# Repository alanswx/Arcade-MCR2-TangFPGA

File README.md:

# Bally Midway MCR2 Arcade Core for Gowin Tang FPGAs

Standalone port of the Bally Midway MCR arcade families for Sipeed Tang
FPGA boards — no MiSTer/HPS required. **MCR-2** (Tron, Domino Man,
Satan's Hollow, Wacko, Kozmik Kroozr, Two Tigers), **MCR-3/91490**
(Tapper — hardware-verified — plus Timber and Discs of Tron), and
**MCR-1** (Kick, Kickman, Solar Fox; builds, unverified). The flagship
target is the **Tang Console 60K**: each family's games in one bitstream,
selected at runtime from an on-screen menu, ROMs loaded from a single
microSD card shared by every family (pack format v2). The roadmap toward
the full-series multi-core jukebox is at the top of TODO.md.

| Board | Status |
|---|---|
| **Tang Console 60K** (GW5AT-60) | MCR-2: all six games + OSD menu. MCR-3: Tapper working (SDRAM sprites), Timber/DoT staged. 720p HDMI with audio (DDR3 framebuffer); analog RGB at 31/15 kHz for real cabinets; USB gamepad; SD ROM loading; <10 s watchdog-guarded cold boot |
| Tang Primer 25K (GW5A-25) | Domino Man over HDMI (single game per build, BSRAM-limited) |
| Tang Console 138K (GW5AST-138) | Stale — needs the 60K backport |

New here? Read [handoff_v7_jukebox.md](handoff_v7_jukebox.md) for the
current platform state and runway.

Deeper docs: build gotchas and architecture notes in [CLAUDE.md](CLAUDE.md),
open issues in [TODO.md](TODO.md), bench hookup in
[docs/bench_wiring.md](docs/bench_wiring.md), cabinet shield spec in
[docs/universal_mcr_shield_spec.md](docs/universal_mcr_shield_spec.md),
porting plan for the other MCR generations in
[docs/mcr_core_roadmap.md](docs/mcr_core_roadmap.md).

---

## 1. Generate the ROM hex tables

ROM zips (MAME sets) go in `roms/` — they are **not** in the repo. Then,
from the repo root:

```sh
python3 tools/merge_roms.py tron     # or domino / shollow / wacko / kroozr / twotiger
```

This writes the `rom_*.hex` tables the build bakes into BSRAM and sets the
board's `game_config.vh`. On the 60K the baked game only decides **what
boots with no SD card** — every game is reachable at runtime from the OSD.

## 2. Build

Headless (recommended; macOS paths shown — see CLAUDE.md for why the IDE
flow needs extra care):

```sh
GWLIB=/Applications/GowinIDE.app/Contents/Resources/Gowin_EDA/IDE/lib
GW=/Applications/GowinIDE.app/Contents/Resources/Gowin_EDA/IDE/bin/gw_sh
cd mcr2_console60k
DYLD_LIBRARY_PATH="$GWLIB" DYLD_FRAMEWORK_PATH="$GWLIB" "$GW" build.tcl
```

The bitstream lands at `mcr2_console60k/impl/pnr/mcr2_console60k.fs`.
Prebuilt images for all six games are kept in `bitstreams/`.

IDE builds work too (open `mcr2_console60k/mcr2_console60k.gprj`, Run All)
but several project settings must be exactly right — read the Gotchas
table in CLAUDE.md first; in particular **Place & Route → Place Option
must be 2** or HDMI silently dies.

## 3. Flash the board

With [openFPGALoader](https://github.com/trabucayre/openFPGALoader)
(`brew install openfpgaloader`), board connected over USB-C:

```sh
# quick test - loads SRAM, lost at power-off
openFPGALoader -b tangconsole bitstreams/console60k_tron.fs

# make it the POWER-ON default - writes the SPI flash
openFPGALoader -b tangconsole -f bitstreams/console60k_tron.fs
```

The `-f` form replaces whatever was in flash (e.g. NESTang) — reflash that
the same way if you want it back. The Gowin Programmer GUI works as well
(External Flash Mode → exFlash Erase, Program).

## 4. Make the SD card (all six games, switchable from the menu)

The ROM pack lives in **raw sectors starting at sector 2048** (1 MiB in) —
no filesystem involved, and it coexists with a normally-formatted card
(standard SD formatting starts the first partition at 4 MiB+; existing
files are untouched).

```sh
python3 tools/make_rompack.py                 # builds mcr_rompack.img from roms/
sudo python3 tools/write_rompack.py           # lists candidate cards
sudo python3 tools/write_rompack.py disk4     # writes + verifies (macOS)
```

`write_rompack.py` refuses to touch anything that is not a removable disk,
refuses cards whose partitions would overlap the pack, and verifies the
header after writing. On Linux/Windows use the `dd`/Win32DiskImager recipe
that `make_rompack.py` prints.

Put the card in the **console's** microSD slot. Every game you select in
the OSD is saved to the card (a reserved sector below the pack), and the
next power-on boots straight back into it - so a cabinet owner picks a
game once and it sticks. With no card (or a blank prefs sector) the
baked-in game boots.

## 5. Play

- **USB gamepad** in the left USB-A port: D-pad = joystick, A = Button 1,
  Start = Start 1, Select = Coin 1 (B/X/Y vary per game — see the input
  maps in `mcr2_console60k_top.sv`).
- **Select+Start opens the game-select menu** on every video output:
  Up/Down move, A loads the highlighted game from the SD card, B exits.
  The screen freezing (HDMI) or dropping sync (analog) for ~1 s after
  pressing A is the ROM reload, not a crash.
- Board keys: AA13 = reset, AB13 = Coin 1.
- HDMI is always live at 720p. Analog RGB comes out of the J10 header
  (31 kHz VGA, or jumper J10-37 to GND for native 15 kHz arcade timing) —
  wiring recipes in [docs/bench_wiring.md](docs/bench_wiring.md).
- A UART status beacon prints on the USB-C serial port (115200 8N1) for
  case-closed debugging — field decoding in docs/bench_wiring.md.

## 6. Cabinet integration

The goal is a drop-in board for real MCR cabinets: analog 15 kHz RGB,
original harness connectors, physical DIPs for game options. For anyone
building the PCB: the **frozen 40-pin header sheet is
[docs/shield_j10_pinout.md](docs/shield_j10_pinout.md)** — one header
carries video, audio and all controls (inputs via a 74HC165 chain that
covers every game, outputs via 74HC595). The consolidated electrical spec
is [docs/universal_mcr_shield_spec.md](docs/universal_mcr_shield_spec.md);
per-game harness pinouts are in
[docs/mcr_game_input_matrix.md](docs/mcr_game_input_matrix.md).

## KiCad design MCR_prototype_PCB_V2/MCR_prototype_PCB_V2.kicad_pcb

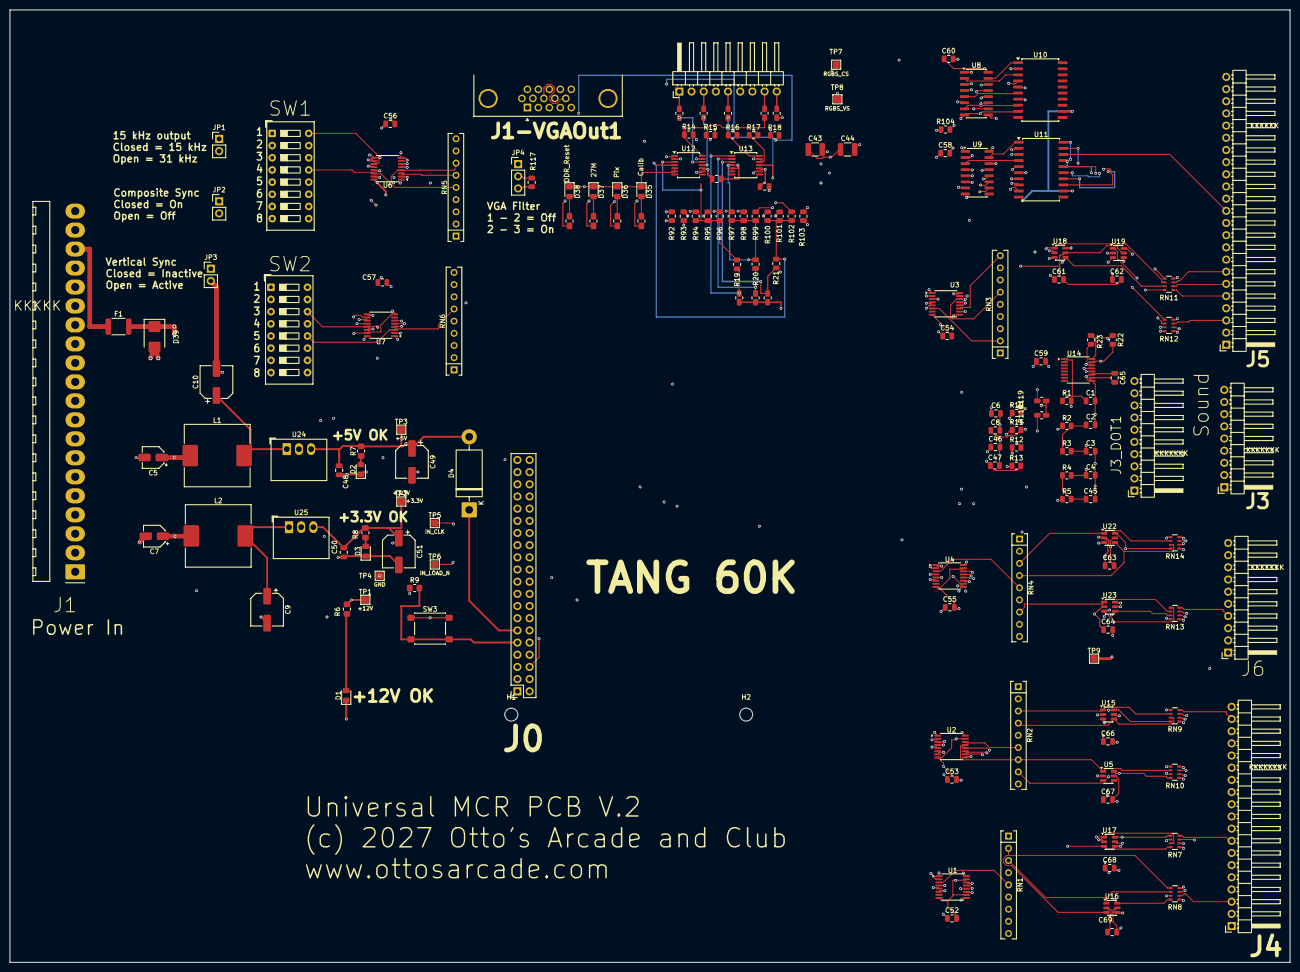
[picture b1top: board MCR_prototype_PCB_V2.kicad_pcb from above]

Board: 4 copper layers, 267.1 x 198.7 mm, 166 parts (0 on the bottom side), 198 nets.

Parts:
C1, C41, C42, C48, C50, C52, C53, C54, C55, C56, C57, C58, C59, C60, C61, C62, C63, C64, C65, C66, C67, C68, C69: 0.1 uF; C_0805_2012Metric
C2, C3, C4, C6, C8, C45, C46, C47: 0.01 uF; C_0805_2012Metric
C5, C7: 4.7 uF 50V; CP_Elec_4x5.4
C9, C10: 10 uF 50V; CP_Elec_6.3x5.4
C43, C44: 22 uF; C_1210_3225Metric
C49, C51: 100 uF; CP_Elec_6.3x5.4
D1, D2, D3, D35, D36, D37, D38: LED; LED_0805_2012Metric_Pad1.15x1.40mm_HandSolder
D4: 1N5822; D_DO-201AD_P15.24mm_Horizontal
D39: SMBJ15A; D_SMB
F1: 2A 24V; Fuse_1812_4532Metric
H1, H2: MountingHole_2.7mm_M2.5
J0: Conn_02x20_Odd_Even; PinSocket_2x20_P2.54mm_Vertical
J1: Conn_01x20_Pin; Molex_KK-396_A-41792-0020_1x20_P3.96mm_Horizontal
J1-VGAOut1: DE15_Socket_HighDensity; DSUB-15-HD_Socket_Horizontal_P2.29x1.90mm_EdgePinOffset3.03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
J2_RGBS_Out1, J3: Conn_01x09_Pin; PinHeader_1x09_P2.54mm_Horizontal
J3_DOT1: Conn_01x10_Pin; PinHeader_1x10_P2.54mm_Horizontal_mirrored
J4: Conn_01x19_Pin; PinHeader_1x19_P2.54mm_Horizontal
J5: Conn_01x23_Pin; PinHeader_1x23_P2.54mm_Horizontal
J6: Conn_01x10_Pin; PinHeader_1x10_P2.54mm_Horizontal
JP1: 15 kHz Select; PinHeader_1x02_P2.54mm_Vertical
JP2: Composite Sync Select; PinHeader_1x02_P2.54mm_Vertical
JP3: Vertical Sync Inactive select; PinHeader_1x02_P2.54mm_Vertical
JP4: VGA Filter; PinHeader_1x03_P2.54mm_Vertical
L1, L2: FAUL1340-3R3MT; L_TechFuse_SL1250
R1, R2, R3, R4, R5, R10, R11, R12, R13, R22, R23, R95, R98, R101: 1k; R_0805_2012Metric
R6: 4.7k ohm; R_0805_2012Metric_Pad1.20x1.40mm_HandSolder
R7: 680 ohm; R_0805_2012Metric_Pad1.20x1.40mm_HandSolder
R8, R108, R109, R110, R111: 330 ohm; R_0805_2012Metric_Pad1.20x1.40mm_HandSolder
R9: 1k; R_0805_2012Metric_Pad1.20x1.40mm_HandSolder
R14, R15, R16, R17, R18, R112, R113, R114, R115, R116: 75; R_0805_2012Metric
R19, R20, R21: 221; R_0805_2012Metric
R92, R93: 100; R_0805_2012Metric
R94, R97, R100: 510; R_0805_2012Metric
R96, R99, R102: 2k; R_0805_2012Metric
R103, R104, R117, R118, R119: 10k; R_0805_2012Metric
R105, R106, R107: 137; R_0805_2012Metric
RN1, RN2, RN3, RN4, RN5, RN6: 4.7k ohm; SIP-9_22.3x3mm_P2.54mm
RN7, RN8, RN9, RN10, RN11, RN12, RN13, RN14: 1K Ohm; R_Array_Convex_4x0603
SW1, SW2: DSIC08LHGET; SW_DIP_SPSTx08_Slide_9.78x22.5mm_W7.62mm_P2.54mm
SW3: PTS645SM43SMTR92LFS; SW_SPST_PTS645Sx43SMTR92
TP1: +12V Input; TestPoint_Pad_1.5x1.5mm
TP2: +3.3V Power; TestPoint_Pad_1.5x1.5mm
TP3: +5V Power; TestPoint_Pad_1.5x1.5mm
TP4: Gnd; TestPoint_Pad_1.5x1.5mm
TP5: In_Clk; TestPoint_Pad_1.5x1.5mm
TP6: IN_LOAD_N; TestPoint_Pad_1.5x1.5mm
TP7: VID_HS; TestPoint_Pad_1.5x1.5mm
TP8: VID_VS; TestPoint_Pad_1.5x1.5mm
TP9: GND; TestPoint_Pad_1.5x1.5mm
U1, U2, U3, U4, U6, U7: 74AHC165; TSSOP-16_4.4x5mm_P0.65mm
U5, U15, U16, U17, U18, U19, U22, U23: SRV05-4; SOT-23-6
U8, U9: SN74AHCT595DR; SOIC-16_3.9x9.9mm_P1.27mm
U10, U11: ULN2803CDWR; SOIC-20W_7.5x12.8mm_P1.27mm
U12, U13: THS7374; TSSOP-14_4.4x5mm_P0.65mm
U14: ADS7830; TSSOP-16_4.4x5mm_P0.65mm
U24: K7805-2000R3; Converter_DCDC_RECOM_R-78B-2.0_THT
U25: K7803-2000R3; Converter_DCDC_RECOM_R-78B-2.0_THT

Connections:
+3.3V: C50.1, C51.1, C52.1, C53.1, C54.1, C55.1, C56.1, C57.1, C59.1, J3.1, J3_DOT1.1, R8.1, R9.1, R22.1, R23.1, R103.1, R104.1, TP2.1 (1_1), U1.16 (VCC), U2.16 (VCC), U3.16 (VCC), U4.16 (VCC), U6.16 (VCC), U7.16 (VCC), U14.16 (VDD), U25.3 (OUT)
+5V: C41.1, C42.1, C43.1, C44.1, C48.1, C49.1, C58.1, C60.1, C61.2, C62.2, C63.2, C64.2, C66.2, C67.2, C68.2, C69.2, D4.2 (A), JP4.1 (A), R7.1, RN1.1 (common), RN2.1 (common), RN3.1 (common), RN4.1 (common), RN5.1 (common), RN6.1 (common), TP3.1 (1_1), U5.5 (VP), U8.16 (VCC), U9.16 (VCC), U12.10 (V_{S+}), U13.10 (V_{S+}), U15.5 (VP), U16.5 (VP), U17.5 (VP), U18.5 (VP), U19.5 (VP), U22.5 (VP), U23.5 (VP), U24.3 (OUT)
+12V: C5.1, C7.1, D39.1 (K), F1.2, L1.1, L2.1, R6.1, TP1.1 (1_1), U10.12 (COM), U11.12 (COM)
/RGBS_CS_OUT: J2_RGBS_Out1.8, R112.2, TP7.1 (1_1)
/RGBS_VS_OUT: J2_RGBS_Out1.9, R113.2, TP8.1 (1_1)
/VGA_B_BUF: R18.1, U13.13 (CH2_OUT)
/VGA_G_BUF: R17.1, U13.12 (CH3_OUT)
/VGA_R_BUF: R16.1, U13.14 (CH1_OUT)
ADC_A0: J0.30, R118.1, U14.12 (A0)
ADC_A1: J0.29, R119.1, U14.13 (A1)
ADC_SCL: J0.20, R23.2, U14.14 (SCL)
ADC_SDA: J0.19, R22.2, U14.15 (SDA)
ARD: J5.16, U11.14 (O7)
AUD_PWM_L1: J0.35, R2.1
AUD_PWM_L2: J0.1, R13.1
AUD_PWM_R1: J0.36, R5.1
AUD_PWM_R2: J0.5, R12.1
GND: C1.2, C2.2, C3.2, C4.2, C5.2, C6.2, C7.2, C8.2, C9.2, C10.2, C41.2, C42.2, C43.2, C44.2, C45.2, C46.2, C47.2, C48.2, C49.2, C50.2, C51.2, C52.2, C53.2, C54.2, C55.2, C56.2, C57.2, C58.2, C59.2, C60.2, C61.1, C62.1, C63.1, C64.1, C65.1, C66.1, C67.1, C68.1, C69.1, D1.1 (K), D2.1 (K), D3.1 (K), D35.1 (K), D36.1 (K), D37.1 (K), D38.1 (K), D39.2 (A), J0.12, J1.6, J1.7, J1.10, J1.20, J1-VGAOut1.5, J1-VGAOut1.6, J1-VGAOut1.7, J1-VGAOut1.8, J1-VGAOut1.10, J2_RGBS_Out1.2, J2_RGBS_Out1.4, J2_RGBS_Out1.6, J3.3, J3.8, J3_DOT1.3, J3_DOT1.5, J3_DOT1.8, J4.9, J4.19, J5.9, J5.18, JP1.2 (B), JP2.2 (B), JP3.2 (B), JP4.3 (B), R105.2, R106.2, R107.2, R117.2, R118.2, R119.2, SW1.1, SW1.2, SW1.3, SW1.4, SW1.5, SW1.6, SW1.7, SW1.8, SW2.1, SW2.2, SW2.3, SW2.4, SW2.5, SW2.6, SW2.7, SW2.8, SW3.1, TP4.1 (1_1), TP9.1 (1_1), U1.8 (GND), U1.10 (DS), U1.15 (~CE), U2.8 (GND), U2.15 (~CE), U3.8 (GND), U3.15 (~CE), U4.8 (GND), U4.15 (~CE), U5.2 (VN), U6.8 (GND), U6.15 (~CE), U7.8 (GND), U7.15 (~CE), U8.8 (GND), U9.8 (GND), U10.9 (GND), U11.9 (GND), U12.5 (GND), U12.6 (DISABLE), U13.5 (GND), U13.6 (DISABLE), U14.9 (GND), U14.11 (COM), U15.2 (VN), U16.2 (VN), U17.2 (VN), U18.2 (VN), U19.2 (VN), U22.2 (VN), U23.2 (VN), U24.2 (GND), U25.2 (GND)
IN_CLK: J0.25, TP5.1 (1_1), U1.2 (CP), U2.2 (CP), U3.2 (CP), U4.2 (CP), U6.2 (CP), U7.2 (CP)
IN_DATA: J0.27, U7.9 (Q7)
IN_LOAD_N: J0.26, TP6.1 (1_1), U1.1 (~PL), U2.1 (~PL), U3.1 (~PL), U4.1 (~PL), U6.1 (~PL), U7.1 (~PL)
J4_Input_Stream: U2.9 (Q7), U3.10 (DS)
J5_Input_Stream: U3.9 (Q7), U4.10 (DS)
J6_Input_Stream: U4.9 (Q7), U6.10 (DS)
LED_27M: J0.23, R110.2
LED_CALIB: J0.21, R108.2
LED_DDR_RST: J0.24, R111.2
LED_PIX: J0.22, R109.2
MD0: J5.10, U11.20 (O1)
MD1: J5.11, U11.19 (O2)
MD2: J5.12, U11.18 (O3)
MD3: J5.13, U11.17 (O4)
MODE_15N: J0.37, JP1.1 (A)
unnamed: C2.1, R2.2, R3.1
unnamed: C45.1, R4.1, R5.2
unnamed: C46.1, R10.1, R12.2
unnamed: C47.1, R11.1, R13.2
unnamed: D1.2 (A), R6.2
unnamed: D2.2 (A), R7.2
unnamed: D3.2 (A), R8.2
unnamed: D4.1 (K), J0.11
unnamed: D35.2 (A), R108.1
unnamed: D36.2 (A), R109.1
unnamed: D37.2 (A), R110.1
unnamed: D38.2 (A), R111.1
unnamed: F1.1, J1.18
unnamed: J1-VGAOut1.1, R16.2
unnamed: J1-VGAOut1.2, R17.2
unnamed: J1-VGAOut1.3, R18.2
unnamed: J1-VGAOut1.13, R14.2
unnamed: J1-VGAOut1.14, R15.2
unnamed: J2_RGBS_Out1.1, R115.2
unnamed: J2_RGBS_Out1.3, R116.2
unnamed: J2_RGBS_Out1.5, R114.2
unnamed: J3.2, J3_DOT1.2, R1.2
unnamed: C4.1, J3.7, J3_DOT1.6, R4.2
unnamed: C3.1, J3.9, J3_DOT1.7, R3.2
unnamed: C6.1, J3_DOT1.9, R10.2
unnamed: C8.1, J3_DOT1.10, R11.2
unnamed: J4.1, RN8.4 (R4.1)
unnamed: J4.2, RN8.3 (R3.1)
unnamed: J4.3, RN8.2 (R2.1)
unnamed: J4.4, RN8.1 (R1.1)
unnamed: J4.5, RN7.1 (R1.1)
unnamed: J4.6, RN7.2 (R2.1)
unnamed: J4.7, RN7.3 (R3.1)
unnamed: J4.8, RN7.4 (R4.1)
unnamed: J4.10, RN10.1 (R1.1)
unnamed: J4.11, RN10.2 (R2.1)
unnamed: J4.12, RN10.3 (R3.1)
unnamed: J4.13, RN10.4 (R4.1)
unnamed: J4.15, RN9.1 (R1.1)
unnamed: J4.16, RN9.2 (R2.1)
unnamed: J4.17, RN9.3 (R3.1)
unnamed: J4.18, RN9.4 (R4.1)
unnamed: J5.1, RN12.1 (R1.1)
unnamed: J5.2, RN12.2 (R2.1)
unnamed: J5.3, RN12.3 (R3.1)
unnamed: J5.4, RN12.4 (R4.1)
unnamed: J5.5, RN11.1 (R1.1)
unnamed: J5.6, RN11.2 (R2.1)
unnamed: J5.7, RN11.3 (R3.1)
unnamed: J5.8, RN11.4 (R4.1)
unnamed: J6.1, RN13.1 (R1.1)
unnamed: J6.2, RN13.2 (R2.1)
unnamed: J6.3, RN13.3 (R3.1)
unnamed: J6.4, RN13.4 (R4.1)
unnamed: J6.5, RN14.1 (R1.1)
unnamed: J6.6, RN14.2 (R2.1)
unnamed: J6.7, RN14.3 (R3.1)
unnamed: J6.9, RN14.4 (R4.1)
unnamed: JP4.2 (C), R117.1, U12.9 (BYPASS), U13.9 (BYPASS)
unnamed: RN1.2 (R1), RN8.5 (R4.2), U1.6 (D7), U16.3 (IO2)
unnamed: RN1.3 (R2), RN8.6 (R3.2), U1.5 (D6), U16.1 (IO1)
unnamed: RN1.4 (R3), RN8.7 (R2.2), U1.4 (D5), U16.4 (IO3)
unnamed: RN1.5 (R4), RN8.8 (R1.2), U1.3 (D4), U16.6 (IO4)
unnamed: RN1.6 (R5), RN7.8 (R1.2), U1.14 (D3), U17.3 (IO2)
unnamed: RN1.7 (R6), RN7.7 (R2.2), U1.13 (D2), U17.1 (IO1)
unnamed: RN1.8 (R7), RN7.6 (R3.2), U1.12 (D1), U17.4 (IO3)
unnamed: RN1.9 (R8), RN7.5 (R4.2), U1.11 (D0), U17.6 (IO4)
unnamed: RN2.2 (R1), RN9.5 (R4.2), U2.6 (D7), U15.3 (IO2)
unnamed: RN2.3 (R2), RN9.6 (R3.2), U2.5 (D6), U15.1 (IO1)
unnamed: RN2.4 (R3), RN9.7 (R2.2), U2.4 (D5), U15.4 (IO3)
unnamed: RN2.5 (R4), RN9.8 (R1.2), U2.3 (D4), U15.6 (IO4)
unnamed: RN5.2 (R1), SW1.16, U6.11 (D0)
unnamed: RN5.3 (R2), SW1.15, U6.12 (D1)
unnamed: RN5.4 (R3), SW1.14, U6.13 (D2)
unnamed: RN5.5 (R4), SW1.13, U6.14 (D3)
unnamed: RN5.6 (R5), SW1.12, U6.3 (D4)
unnamed: RN5.7 (R6), SW1.11, U6.4 (D5)
unnamed: RN5.8 (R7), SW1.10, U6.5 (D6)
unnamed: RN5.9 (R8), SW1.9, U6.6 (D7)
unnamed: RN6.2 (R1), SW2.16, U7.11 (D0)
unnamed: RN6.3 (R2), SW2.15, U7.12 (D1)
unnamed: RN6.4 (R3), SW2.14, U7.13 (D2)
unnamed: RN6.5 (R4), SW2.13, U7.14 (D3)
unnamed: RN6.6 (R5), SW2.12, U7.3 (D4)
unnamed: RN6.7 (R6), SW2.11, U7.4 (D5)
unnamed: RN6.8 (R7), SW2.10, U7.5 (D6)
unnamed: RN6.9 (R8), SW2.9, U7.6 (D7)
unnamed: RN2.9 (R8), RN10.8 (R1.2), U2.11 (D0), U5.6 (IO4)
unnamed: RN2.8 (R7), RN10.7 (R2.2), U2.12 (D1), U5.4 (IO3)
unnamed: RN2.7 (R6), RN10.6 (R3.2), U2.13 (D2), U5.1 (IO1)
unnamed: RN2.6 (R5), RN10.5 (R4.2), U2.14 (D3), U5.3 (IO2)
unnamed: RN3.5 (R4), RN11.8 (R1.2), U3.3 (D4), U18.6 (IO4)
unnamed: RN3.4 (R3), RN11.7 (R2.2), U3.4 (D5), U18.4 (IO3)
unnamed: RN3.3 (R2), RN11.6 (R3.2), U3.5 (D6), U18.1 (IO1)
unnamed: RN3.2 (R1), RN11.5 (R4.2), U3.6 (D7), U18.3 (IO2)
unnamed: RN3.9 (R8), RN12.8 (R1.2), U3.11 (D0), U19.6 (IO4)
unnamed: RN3.8 (R7), RN12.7 (R2.2), U3.12 (D1), U19.4 (IO3)
unnamed: RN3.7 (R6), RN12.6 (R3.2), U3.13 (D2), U19.1 (IO1)
unnamed: RN3.6 (R5), RN12.5 (R4.2), U3.14 (D3), U19.3 (IO2)
unnamed: RN4.9 (R8), RN13.8 (R1.2), U4.11 (D0), U23.6 (IO4)
unnamed: RN4.8 (R7), RN13.7 (R2.2), U4.12 (D1), U23.4 (IO3)
unnamed: RN4.7 (R6), RN13.6 (R3.2), U4.13 (D2), U23.1 (IO1)
unnamed: RN4.6 (R5), RN13.5 (R4.2), U4.14 (D3), U23.3 (IO2)
unnamed: RN4.5 (R4), RN14.8 (R1.2), U4.3 (D4), U22.6 (IO4)
unnamed: RN4.4 (R3), RN14.7 (R2.2), U4.4 (D5), U22.4 (IO3)
unnamed: RN4.3 (R2), RN14.6 (R3.2), U4.5 (D6), U22.1 (IO1)
unnamed: RN4.2 (R1), RN14.5 (R4.2), U4.6 (D7), U22.3 (IO2)
unnamed: U1.9 (Q7), U2.10 (DS)
unnamed: U8.9 (QH'), U9.14 (SER)
unnamed: U8.15 (QA), U10.1 (I1)
unnamed: U8.1 (QB), U10.2 (I2)
unnamed: U8.2 (QC), U10.3 (I3)
unnamed: U8.3 (QD), U10.4 (I4)
unnamed: U8.4 (QE), U10.5 (I5)
unnamed: U8.5 (QF), U10.6 (I6)
unnamed: U8.6 (QG), U10.7 (I7)
unnamed: U8.7 (QH), U10.8 (I8)
unnamed: U9.15 (QA), U11.1 (I1)
unnamed: U9.1 (QB), U11.2 (I2)
unnamed: U9.2 (QC), U11.3 (I3)
unnamed: U9.3 (QD), U11.4 (I4)
unnamed: U9.4 (QE), U11.5 (I5)
unnamed: U9.5 (QF), U11.6 (I6)
unnamed: U9.6 (QG), U11.7 (I7)
unnamed: U9.7 (QH), U11.8 (I8)
unnamed: R92.2, U12.1 (CH1_IN)
unnamed: R14.1, R112.1, U12.14 (CH1_OUT)
unnamed: R93.2, U12.2 (CH2_IN)
unnamed: R15.1, R113.1, U12.13 (CH2_OUT)
unnamed: R19.1, R94.1, R95.1, R96.1, U12.3 (CH3_IN)
unnamed: R115.1, U12.12 (CH3_OUT)
unnamed: R21.1, R100.1, R101.1, R102.1, U12.4 (CH4_IN)
unnamed: R116.1, U12.11 (CH4_OUT)
unnamed: R19.2, R105.1, U13.1 (CH1_IN)
unnamed: R20.2, R106.1, U13.2 (CH2_IN)
unnamed: R21.2, R107.1, U13.3 (CH3_IN)
unnamed: R20.1, R97.1, R98.1, R99.1, U13.4 (CH4_IN)
unnamed: R114.1, U13.11 (CH4_OUT)
unnamed: C1.1, R1.1, U14.1 (CH0)
unnamed: C65.2, U14.10 (REFin/REFout)
unnamed: C10.1, L1.2, U24.1 (IN)
unnamed: C9.1, L2.2, U25.1 (IN)
Out_Clear: J0.33, R104.2, U8.10 (~SRCLR), U9.10 (~SRCLR)
Out_Clock: J0.28, U8.11 (SRCLK), U9.11 (SRCLK)
Out_Data: J0.31, U8.14 (SER)
Out_En_N: J0.34, R103.2, U8.13 (~OE), U9.13 (~OE)
Out_Latch: J0.32, U8.12 (RCLK), U9.12 (RCLK)
SEL: J5.17, U11.13 (O8)
ST0: J5.14, U11.16 (O5)
ST1: J5.15, U11.15 (O6)
SW1_Input_Stream: U6.9 (Q7), U7.10 (DS)
SYNC_CSYNC_N: J0.39, JP2.1 (A)
SYNC_VSOFF_N: J0.40, JP3.1 (A)
Service Switch: J0.9, R9.2, SW3.2
VID_B1: J0.6, R99.2
VID_B2: J0.7, R98.2
VID_B3: J0.8, R97.2
VID_G1: J0.14, R102.2
VID_G2: J0.15, R101.2
VID_G3: J0.16, R100.2
VID_HS: J0.17, R92.1
VID_R1: J0.2, R96.2
VID_R2: J0.3, R95.2
VID_R3: J0.4, R94.2
VID_VS: J0.18, R93.1

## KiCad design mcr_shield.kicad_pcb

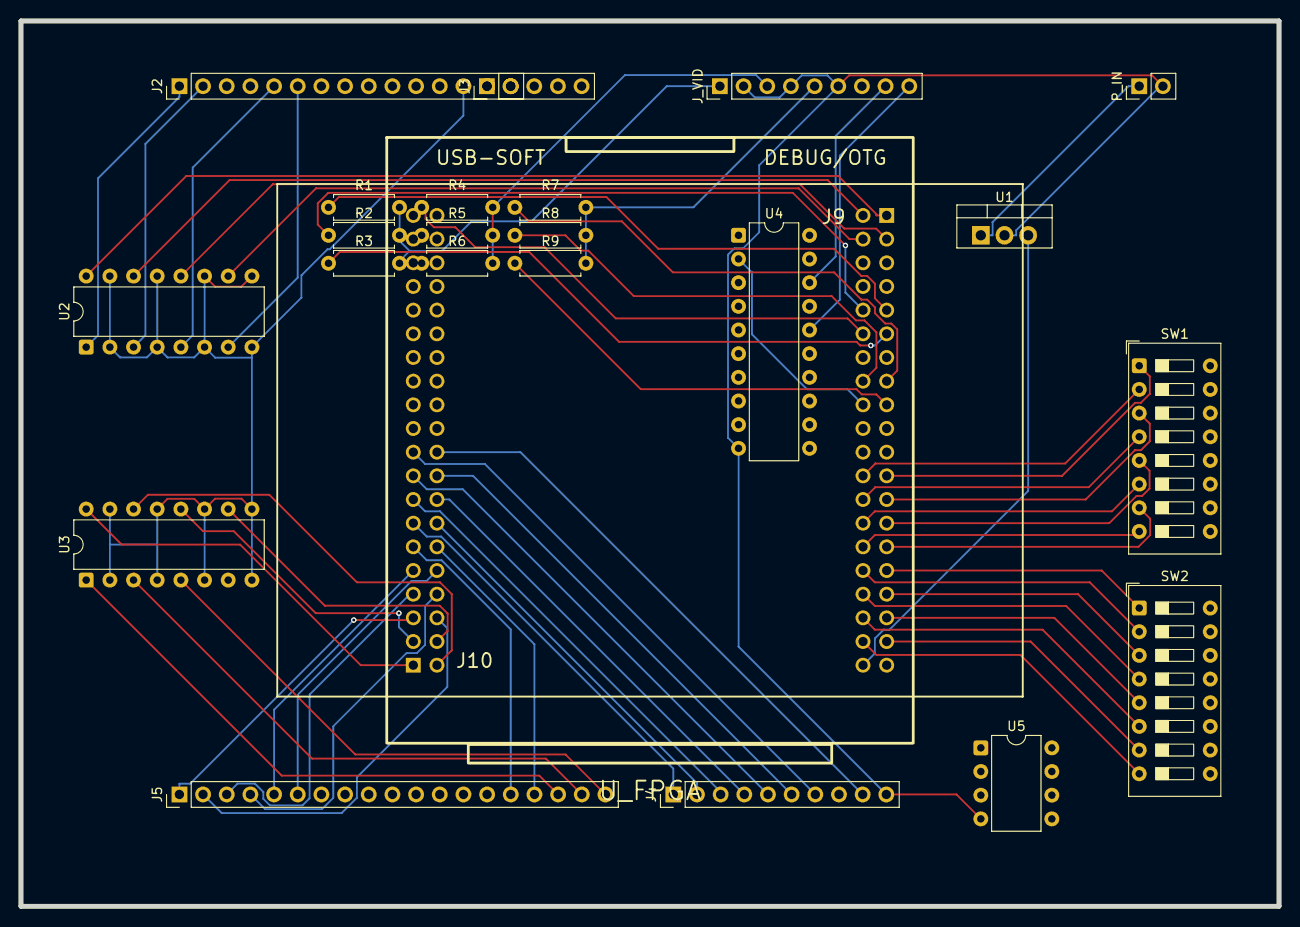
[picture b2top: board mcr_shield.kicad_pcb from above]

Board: 2 copper layers, 135.0 x 95.0 mm, 23 parts (0 on the bottom side), 66 nets.

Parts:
J2: MCR_P1_Controls; PinHeader_1x15_P2.54mm_Vertical
J3: MCR_System_Coin; PinHeader_1x05_P2.54mm_Vertical
J4: MCR_Opt_X_Dial; PinHeader_1x10_P2.54mm_Vertical
J5: MCR_P2_Controls; PinHeader_1x19_P2.54mm_Vertical
J_VID: MCR_Video_Out; PinHeader_1x09_P2.54mm_Vertical
P_IN: Power_+12V_GND; PinHeader_1x02_P2.54mm_Vertical
R1: 3.9k_Red_LSB; R_Axial_DIN0207_L6.3mm_D2.5mm_P7.62mm_Horizontal
R2: 2.0k_Red_Mid; R_Axial_DIN0207_L6.3mm_D2.5mm_P7.62mm_Horizontal
R3: 1.0k_Red_MSB; R_Axial_DIN0207_L6.3mm_D2.5mm_P7.62mm_Horizontal
R4: 3.9k_Green_LSB; R_Axial_DIN0207_L6.3mm_D2.5mm_P7.62mm_Horizontal
R5: 2.0k_Green_Mid; R_Axial_DIN0207_L6.3mm_D2.5mm_P7.62mm_Horizontal
R6: 1.0k_Green_MSB; R_Axial_DIN0207_L6.3mm_D2.5mm_P7.62mm_Horizontal
R7: 3.9k_Blue_LSB; R_Axial_DIN0207_L6.3mm_D2.5mm_P7.62mm_Horizontal
R8: 2.0k_Blue_Mid; R_Axial_DIN0207_L6.3mm_D2.5mm_P7.62mm_Horizontal
R9: 1.0k_Blue_MSB; R_Axial_DIN0207_L6.3mm_D2.5mm_P7.62mm_Horizontal
SW1: Game_Selector; SW_DIP_SPSTx08_Slide_9.78x22.5mm_W7.62mm_P2.54mm
SW2: Cabinet_Options; SW_DIP_SPSTx08_Slide_9.78x22.5mm_W7.62mm_P2.54mm
U1: Buck_Regulator; TO-220-3_Vertical
U2: Optocoupler_P1; DIP-16_W7.62mm
U3: Optocoupler_Sys; DIP-16_W7.62mm
U4: Sync_Buffer; DIP-20_W7.62mm
U5: Audio_Amplifier; DIP-8_W7.62mm
U_FPGA: TangMega138K_Console

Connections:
5V_REGULATED: U1.3, U_FPGA.J9_40
12V_POWER: P_IN.1, U1.1
BTN_FIRE: U2.12, U_FPGA.J9_3
BTN_LEFT: U2.16, U_FPGA.J9_1
BTN_RIGHT: U2.14, U_FPGA.J9_2
BTN_SHIELD: U2.10, U_FPGA.J9_4
CAB_BLUE: J_VID.5, R7.2, R8.2, R9.2
CAB_BTN_FIRE: J2.5, U2.5
CAB_BTN_LEFT: J2.1, U2.1
CAB_BTN_RIGHT: J2.2, U2.3
CAB_BTN_SHIELD: J2.6, U2.7
CAB_GREEN: J_VID.3, R4.2, R5.2, R6.2
CAB_HSYNC: J_VID.8, U4.18
CAB_P2_FIRE: J5.19, U3.5
CAB_P2_LEFT: J5.17, U3.1
CAB_P2_RIGHT: J5.18, U3.3
CAB_RED: J_VID.1, R1.2, R2.2, R3.2
CAB_VSYNC: J_VID.9, U4.16
FPGA_B0: R7.1, U_FPGA.J9_15
FPGA_B1: R8.1, U_FPGA.J9_16
FPGA_B2: R9.1, U_FPGA.J9_17
FPGA_G0: R4.1, U_FPGA.J9_12
FPGA_G1: R5.1, U_FPGA.J9_13
FPGA_G2: R6.1, U_FPGA.J9_14
FPGA_HSYNC: U4.2, U_FPGA.J9_18
FPGA_R0: R1.1, U_FPGA.J9_9
FPGA_R1: R2.1, U_FPGA.J9_10
FPGA_R2: R3.1, U_FPGA.J9_11
FPGA_VSYNC: U4.4, U_FPGA.J9_19
GAME_OPT0: SW2.1, U_FPGA.J9_31
GAME_OPT1: SW2.2, U_FPGA.J9_32
GAME_OPT2: SW2.3, U_FPGA.J9_33
GAME_OPT3: SW2.4, U_FPGA.J9_34
GAME_OPT4: SW2.5, U_FPGA.J9_35
GAME_OPT5: SW2.6, U_FPGA.J9_36
GAME_OPT6: SW2.7, U_FPGA.J9_37
GAME_OPT7: SW2.8, U_FPGA.J9_38
GAME_SEL0: SW1.1, U_FPGA.J9_23
GAME_SEL1: SW1.2, U_FPGA.J9_24
GAME_SEL2: SW1.3, U_FPGA.J9_25
GAME_SEL3: SW1.4, U_FPGA.J9_26
GAME_SEL4: SW1.5, U_FPGA.J9_27
GAME_SEL5: SW1.6, U_FPGA.J9_28
GAME_SEL6: SW1.7, U_FPGA.J9_29
GAME_SEL7: SW1.8, U_FPGA.J9_30
GND: J2.13, J4.10, J_VID.2, J_VID.4, J_VID.6, P_IN.2, U1.2, U2.2, U2.4, U2.6, U2.8, U2.9, U2.11, U2.13, U2.15, U3.2, U3.4, U3.6, U3.8, U3.9, U3.11, U3.13, U3.15, U4.10, U5.4
P2_FIRE: U3.12, U_FPGA.J10_3
P2_LEFT: U3.16, U_FPGA.J10_1
P2_RIGHT: U3.14, U_FPGA.J10_2
P2_SHIELD: U3.10, U_FPGA.J10_4
P2_TRACK_D0: J5.1, U_FPGA.J10_5
P2_TRACK_D1: J5.2, U_FPGA.J10_6
P2_TRACK_D2: J5.3, U_FPGA.J10_7
P2_TRACK_D3: J5.4, U_FPGA.J10_8
P2_TRACK_D4: J5.5, U_FPGA.J10_9
P2_TRACK_D5: J5.6, U_FPGA.J10_10
P2_TRACK_D6: J5.15, U_FPGA.J10_11
P2_TRACK_D7: J5.16, U_FPGA.J10_12
SPINNER_D0: J4.1, U_FPGA.J10_13
SPINNER_D1: J4.2, U_FPGA.J10_14
SPINNER_D2: J4.3, U_FPGA.J10_15
SPINNER_D3: J4.4, U_FPGA.J10_16
SPINNER_D4: J4.5, U_FPGA.J10_17
SPINNER_D5: J4.6, U_FPGA.J10_18
SPINNER_D6: J4.7, U_FPGA.J10_19
SPINNER_D7: J4.9, U_FPGA.J10_20

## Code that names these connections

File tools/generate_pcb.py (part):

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        ("P2_TRACK_D7",     "J5", "16",  "U_FPGA", "J10_12"),

        # J4 Spinner / Dial connections (D0 - D7)
        ("SPINNER_D0",      "J4", "1",   "U_FPGA", "J10_13"),
        ("SPINNER_D1",      "J4", "2",   "U_FPGA", "J10_14"),
        ("SPINNER_D2",      "J4", "3",   "U_FPGA", "J10_15"),
        ("SPINNER_D3",      "J4", "4",   "U_FPGA", "J10_16"),
        ("SPINNER_D4",      "J4", "5",   "U_FPGA", "J10_17"),
        ("SPINNER_D5",      "J4", "6",   "U_FPGA", "J10_18"),
        ("SPINNER_D6",      "J4", "7",   "U_FPGA", "J10_19"),
        ("SPINNER_D7",      "J4", "9",   "U_FPGA", "J10_20"),

        # R2R Video DAC - Input from FPGA Header to Pad 1 of Resistors
        ("FPGA_R0",         "U_FPGA", "J9_9",   "R1", "1"),
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

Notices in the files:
MCR_prototype_PCB_V2/MCR_prototype_PCB_V2.kicad_pcb:
(c) 2027 Otto's Arcade and Club
